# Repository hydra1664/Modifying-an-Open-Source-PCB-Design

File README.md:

# Arduino Nano USB-C Modification

## Overview
This project is a reverse-engineered and modified version of an open-source Arduino Nano clone.  
The idea was to explore PCB design changes in KiCad, upgrade the board to modern standards, and document the process.  

## Base Design
- Board chosen: Arduino Nano clone from KiCad’s open-source library  
- Why this board?  
  - Simple but widely used in prototyping and embedded projects  
  - Compact design with just enough complexity for meaningful modifications  
  - A great test case for experimenting with USB connector upgrades  

## Modifications
### 1. USB-C Connector Upgrade
- Replaced the legacy Micro-USB port with a USB-C connector  
- Chose a compact footprint that fit the Nano’s small PCB without major rerouting  
- Makes the board more user-friendly and future-proof  

### 2. Added 5.1kΩ Pull-Down Resistors
- Two 5.1kΩ resistors added on CC1 and CC2 pins  
- Ensures proper USB-C configuration and reliable detection  

### 3. Improved Routing with Vias
- Added multiple ground and signal vias near the USB-C connector  
- Helps maintain clean return paths and improves signal integrity  

## Verification
- Ran KiCad’s Design Rule Check (DRC) after modifications  
- No clearance, spacing, or connectivity issues were found  

## Images
The repository includes images showing the original and modified design:

### Original_DRC.png

### Modified_DRC.png

### Original_Schematics.png

### Modified_Schematics.png

### Zoomed_Original_Schematics.png

### Zoomed_Modified_Schematics.png  

## Project Files
- Modified KiCad project files  
- Before/after schematics and DRC results  
- Screenshots for visual comparison  

## Tools Used
- KiCad (open-source EDA tool)  

## Learnings
- How to properly select and fit a USB-C footprint on a compact board  
- The importance of routing discipline and signal return paths  
- Making small but meaningful hardware improvements that modernize older designs

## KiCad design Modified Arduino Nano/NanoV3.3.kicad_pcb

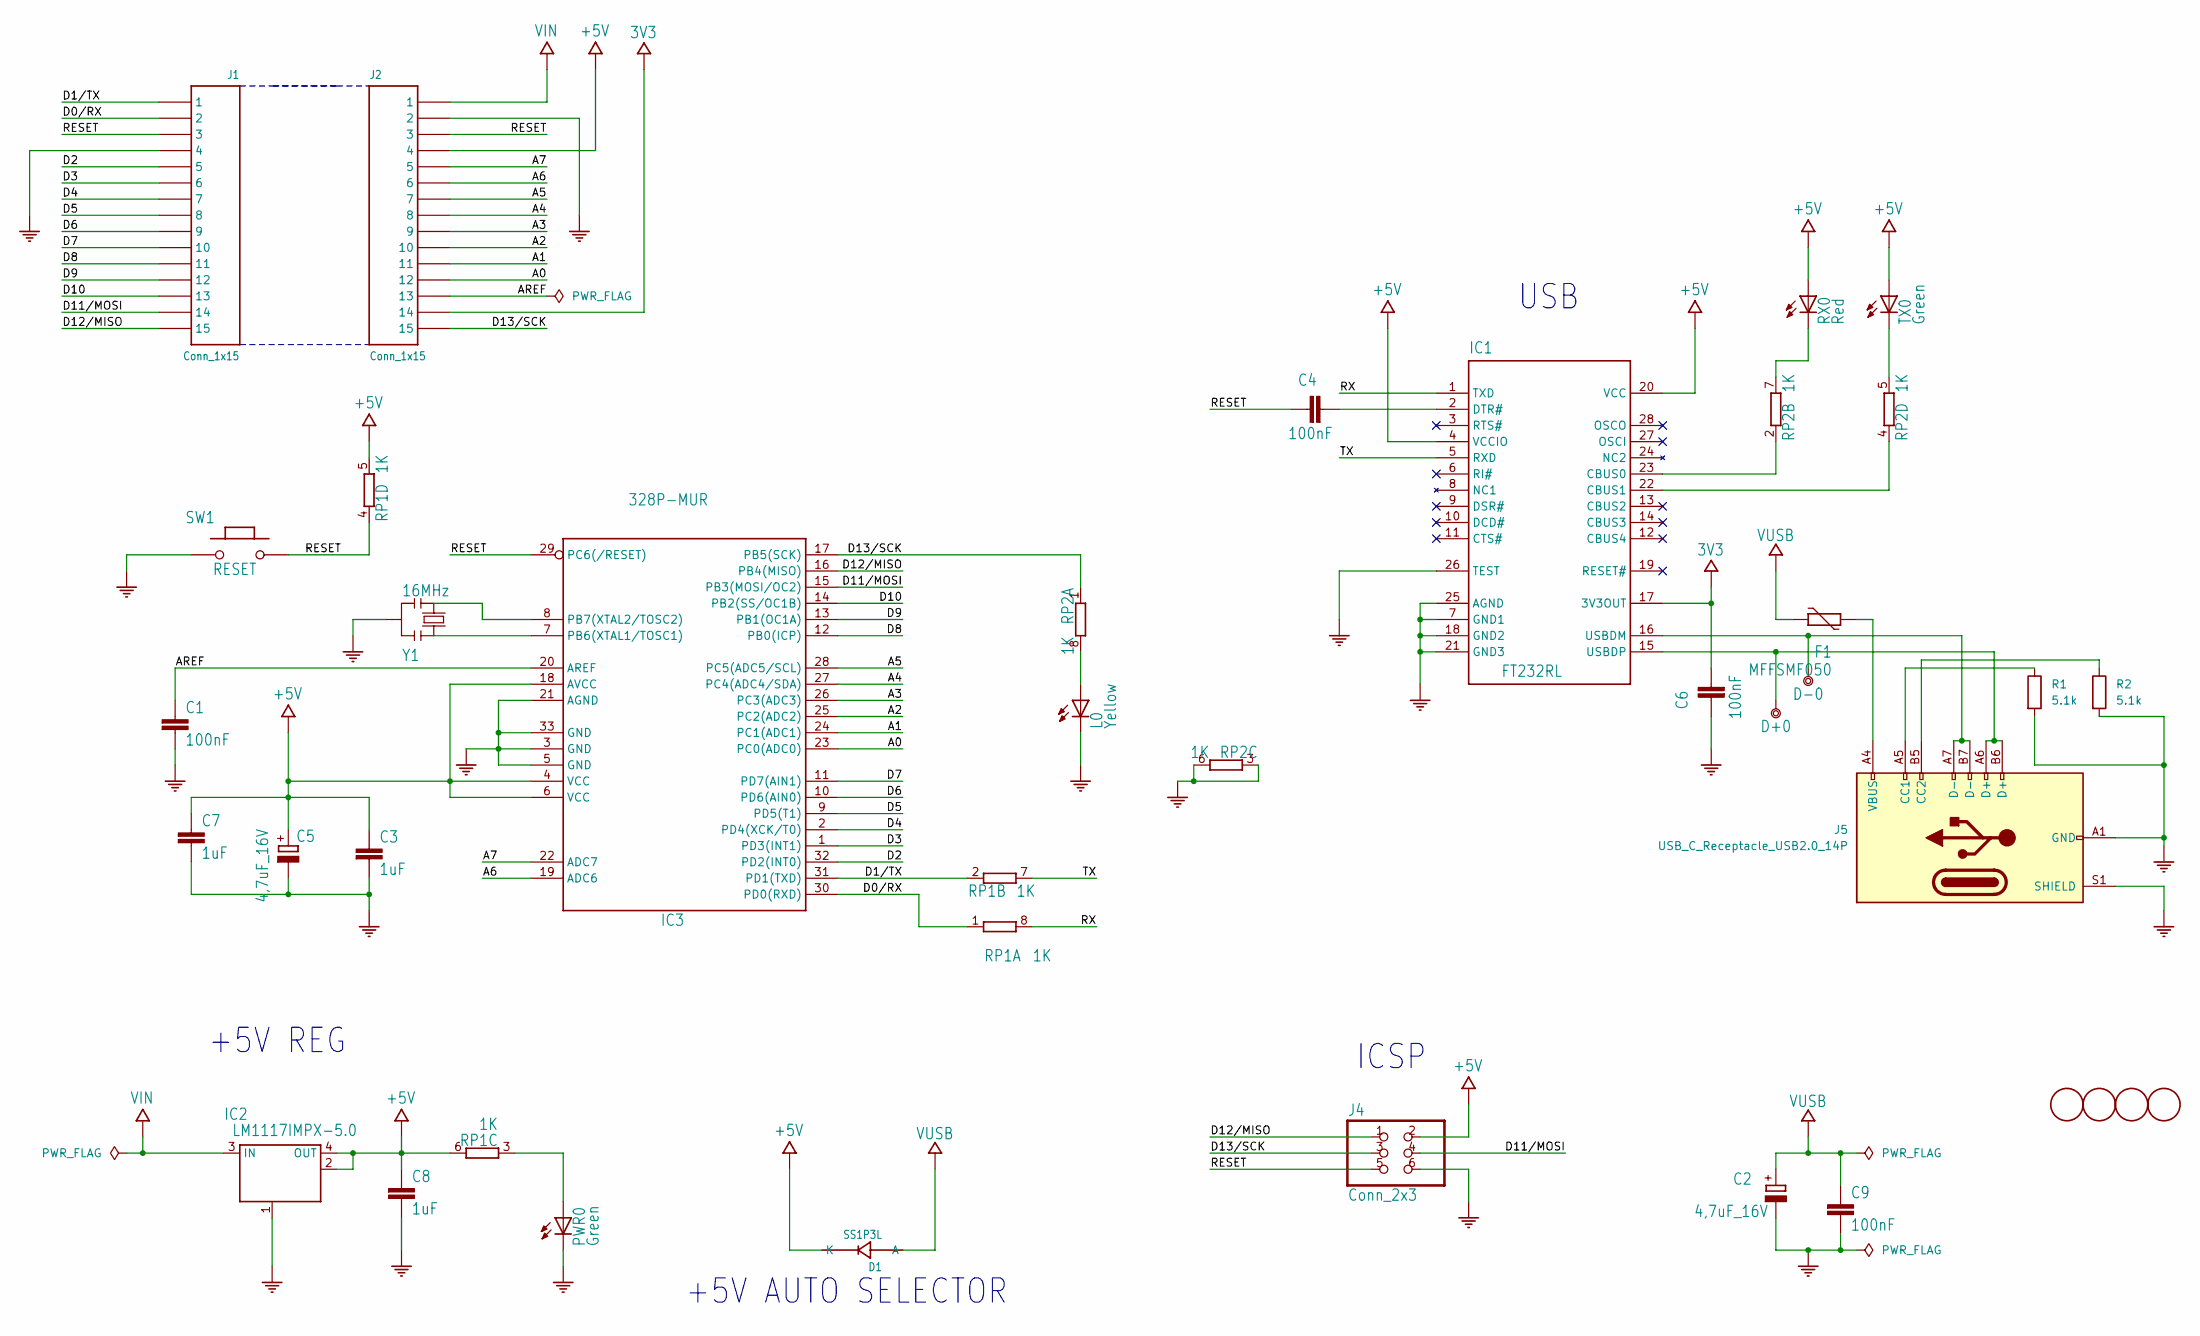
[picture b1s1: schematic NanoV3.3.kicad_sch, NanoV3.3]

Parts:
C1, C4, C6, C9: 100nF; C_0603_1608Metric
C2, C5: 4,7uF_16V; CP_EIA-3216-18_Kemet-A
C3, C7, C8: 1uF; C_0603_1608Metric
D1: SS1P3L; DO-220AA
D+0: DNP; TestPoint_Pad_D1.0mm
D-0: DNP; TestPoint_Pad_D1.0mm
F1: MFFSMF050; Fuse_0603_1608Metric
FD1, FD2, FD3, FD4: DNP; Fiducial_1mm_Mask1.5mm
IC1: FT232RL; SSOP-28_5.3x10.2mm_P0.65mm
IC2: LM1117IMPX-5.0; SOT-223
IC3: 328P-MUR; VQFN-32-1EP_5x5mm_P0.5mm_EP3.254x3.254mm
J1, J2: Conn_1x15; PinHeader_1x15_P2.54mm_Vertical
J4: Conn_2x3; PinHeader_2x3_P2.54mm_Vertical
J5: USB_C_Receptacle_USB2.0_14P; USB_C_Plug_ShenzhenJingTuoJin_918-118A2021Y40002_Vertical
L0: Yellow; LED_0805_2012Metric
PWR0: Green; LED_0805_2012Metric
R1, R2: 5.1k; C_0603_1608Metric
RP1, RP2: 1K; R_CAY16-4
RX0: Red; LED_0805_2012Metric
SW1: RESET; SW_SPST_3.9x2.9mm
TX0: Green; LED_0805_2012Metric
Y1: 16MHz; Resonator_SMD_Murata_CSTxExxV-3Pin_3.0x1.1mm

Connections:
3V3: C6.2, IC1.17 (3V3OUT), J2.14
+5V: C3.1, C5.1 (+), C7.1, C8.1, D1.1 (K), IC1.4 (VCCIO), IC1.20 (VCC), IC2.2, IC2.4 (OUT), IC3.4 (VCC), IC3.6 (VCC), IC3.18 (AVCC), J2.4, J4.2, RP1.5 (2), RP1.6 (2), RX0.1, TX0.1
/A0: IC3.23 (PC0(ADC0)), J2.12
/A1: IC3.24 (PC1(ADC1)), J2.11
/A2: IC3.25 (PC2(ADC2)), J2.10
/A3: IC3.26 (PC3(ADC3)), J2.9
/A4: IC3.27 (PC4(ADC4/SDA)), J2.8
/A5: IC3.28 (PC5(ADC5/SCL)), J2.7
/A6: IC3.19 (ADC6), J2.6
/A7: IC3.22 (ADC7), J2.5
/AREF: C1.1, IC3.20 (AREF), J2.13
/D0/RX: IC3.30 (PD0(RXD)), J1.2, RP1.1
/D1/TX: IC3.31 (PD1(TXD)), J1.1, RP1.2 (1)
/D2: IC3.32 (PD2(INT0)), J1.5
/D3: IC3.1 (PD3(INT1)), J1.6
/D4: IC3.2 (PD4(XCK/T0)), J1.7
/D5: IC3.9 (PD5(T1)), J1.8
/D6: IC3.10 (PD6(AIN0)), J1.9
/D7: IC3.11 (PD7(AIN1)), J1.10
/D8: IC3.12 (PB0(ICP)), J1.11
/D9: IC3.13 (PB1(OC1A)), J1.12
/D10: IC3.14 (PB2(SS/OC1B)), J1.13
/D11/MOSI: IC3.15 (PB3(MOSI/OC2)), J1.14, J4.4
/D12/MISO: IC3.16 (PB4(MISO)), J1.15, J4.1
/D13/SCK: IC3.17 (PB5(SCK)), J2.15, J4.3, RP2.1
/RESET: C4.1, IC3.29 (PC6(/RESET)), J1.3, J2.3, J4.5, RP1.4 (1), SW1.2
/RX: IC1.1 (TXD), RP1.8 (2)
/TX: IC1.5 (RXD), RP1.7 (2)
COM: C1.2, C2.2 (-), C3.2, C5.2 (-), C6.1, C7.2, C8.2, C9.2, IC1.7 (GND1), IC1.18 (GND2), IC1.21 (GND3), IC1.25 (AGND), IC1.26 (TEST), IC2.1 (GND/ADJ), IC3.3 (GND), IC3.5 (GND), IC3.21 (AGND), IC3.33 (GND), J1.4, J2.2, J4.6, J5.A1 (GND), J5.A12 (GND), J5.B1 (GND), J5.B12 (GND), J5.S1 (SHIELD), L0.2, PWR0.2, R1.2, R2.2, RP2.3 (1), RP2.6 (2), SW1.1, Y1.2
unnamed: D+0.X, IC1.15 (USBDP), J5.A6 (D+), J5.B6 (D+)
unnamed: D-0.X, IC1.16 (USBDM), J5.A7 (D-), J5.B7 (D-)
unnamed: F1.2, J5.A4 (VBUS), J5.A9 (VBUS), J5.B4 (VBUS), J5.B9 (VBUS)
unnamed: IC1.23 (CBUS0), RP2.2 (1)
unnamed: IC1.22 (CBUS1), RP2.4 (1)
unnamed: C4.2, IC1.2 (DTR#)
unnamed: IC3.7 (PB6(XTAL1/TOSC1)), Y1.1
unnamed: IC3.8 (PB7(XTAL2/TOSC2)), Y1.3
unnamed: J5.A5 (CC1), R1.1
unnamed: J5.B5 (CC2), R2.1
unnamed: PWR0.1, RP1.3 (1)
unnamed: L0.1, RP2.8 (2)
unnamed: RP2.7 (2), RX0.2
unnamed: RP2.5 (2), TX0.2
VIN: IC2.3 (IN), J2.1
VUSB: C2.1 (+), C9.1, D1.2 (A), F1.1

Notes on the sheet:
+5V REG
+5V AUTO SELECTOR
ICSP
USB

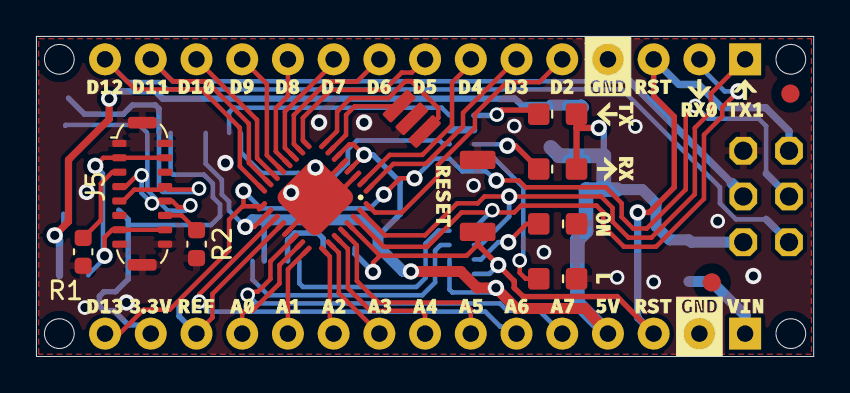
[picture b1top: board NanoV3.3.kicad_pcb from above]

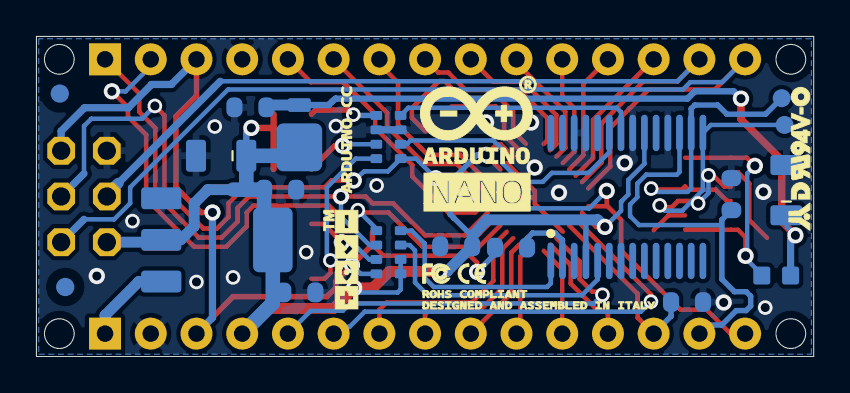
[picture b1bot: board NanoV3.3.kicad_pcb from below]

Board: 2 copper layers, 43.2 x 17.8 mm, 36 parts (20 on the bottom side), 45 nets.

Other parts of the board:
Silkscreen_Back: Silkscreen_Front; Silkscreen_Back
Silkscreen_Front: Silkscreen_Back; Silkscreen_Front

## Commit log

2025-08-20 Added Images
2025-08-20 Upoaded project files
